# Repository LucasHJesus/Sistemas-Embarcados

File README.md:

# PAINEL SOLAR SEGUIDOR DE SOL
# (SUN TRACKING SOLAR PANEL)
## Projeto final da matéria de sistemas embarcados

Lucas Humberto Jesus de Lima - 12011ECP011

Bruno Pavan Ciriani da SIlva - 12011ECP012

## Objetivo
 
  O projeto tem como finalidade a construção de um circuito que controla a
rotação(posição relativa) de um painel solar baseado na incidência luminosa, de forma a
maximizar a irradiação na superfície da placa. Tal tarefa é realizada por meio da utilização de
sensores LDR(posicionados nas bordas da placa), cuja medição serve de referência para
rotação em torno do eixo de um servo motor.
Dados como energia gerada em tempo real serão monitorados, exibidos em um display
LCD e armazenados em uma memória externa.

## Principais Requisitos
Para o funcionamento adequado do projeto, existem certos requisitos, como os
seguintes componentes:

* Painel Solar
* Microcontrolador STM32F411CE
* 2 Sensores LDR
* 3 Resistores de 10kΩ
* Servo Motor
* Push Button (NA)
* Placa para apoio do painel solar
* Fios de conexão
* Bateria 9V
* Regulador de Tensão
* Display LCD
* Memória externa e adaptador
* Resistores para medição da energia gerada
  As funções dos principais componentes são:

  Painel Solar : Transforma energia luminosa em energia elétrica.
  
 STM32F411CE: Microcontrolador usado para comparar os sinais enviados e coordenar o
funcionamento dos demais componentes do projeto.

 Sensores LDR: Geram diferentes valores de resistência de acordo com a incidência de luz solar
sobre eles, para serem comparados pelo microcontrolador.
  
 Servo Motor: Rotaciona a placa na direção desejada.

 Push Button: Habilita(ou desabilita) a alimentação do circuito.

 Bateria 9V: Alimentar os componentes do circuito.
  
 Regulador de Tensão: Regula o valor de tensão para o valor usado pelos componentes do
circuito.

  Display: Exibe dados de interesse coletados pelo circuito medidor em tempo real.

  Memória Externa: Armazena dados de interesse coletados pelo circuito medidor.

  Resistores para medição da energia gerada: Divisor de tensão com o intuito de limitar o valor
em 3.3V para que possa ser medido pelo microcontrolador.

## Diagrama de blocos

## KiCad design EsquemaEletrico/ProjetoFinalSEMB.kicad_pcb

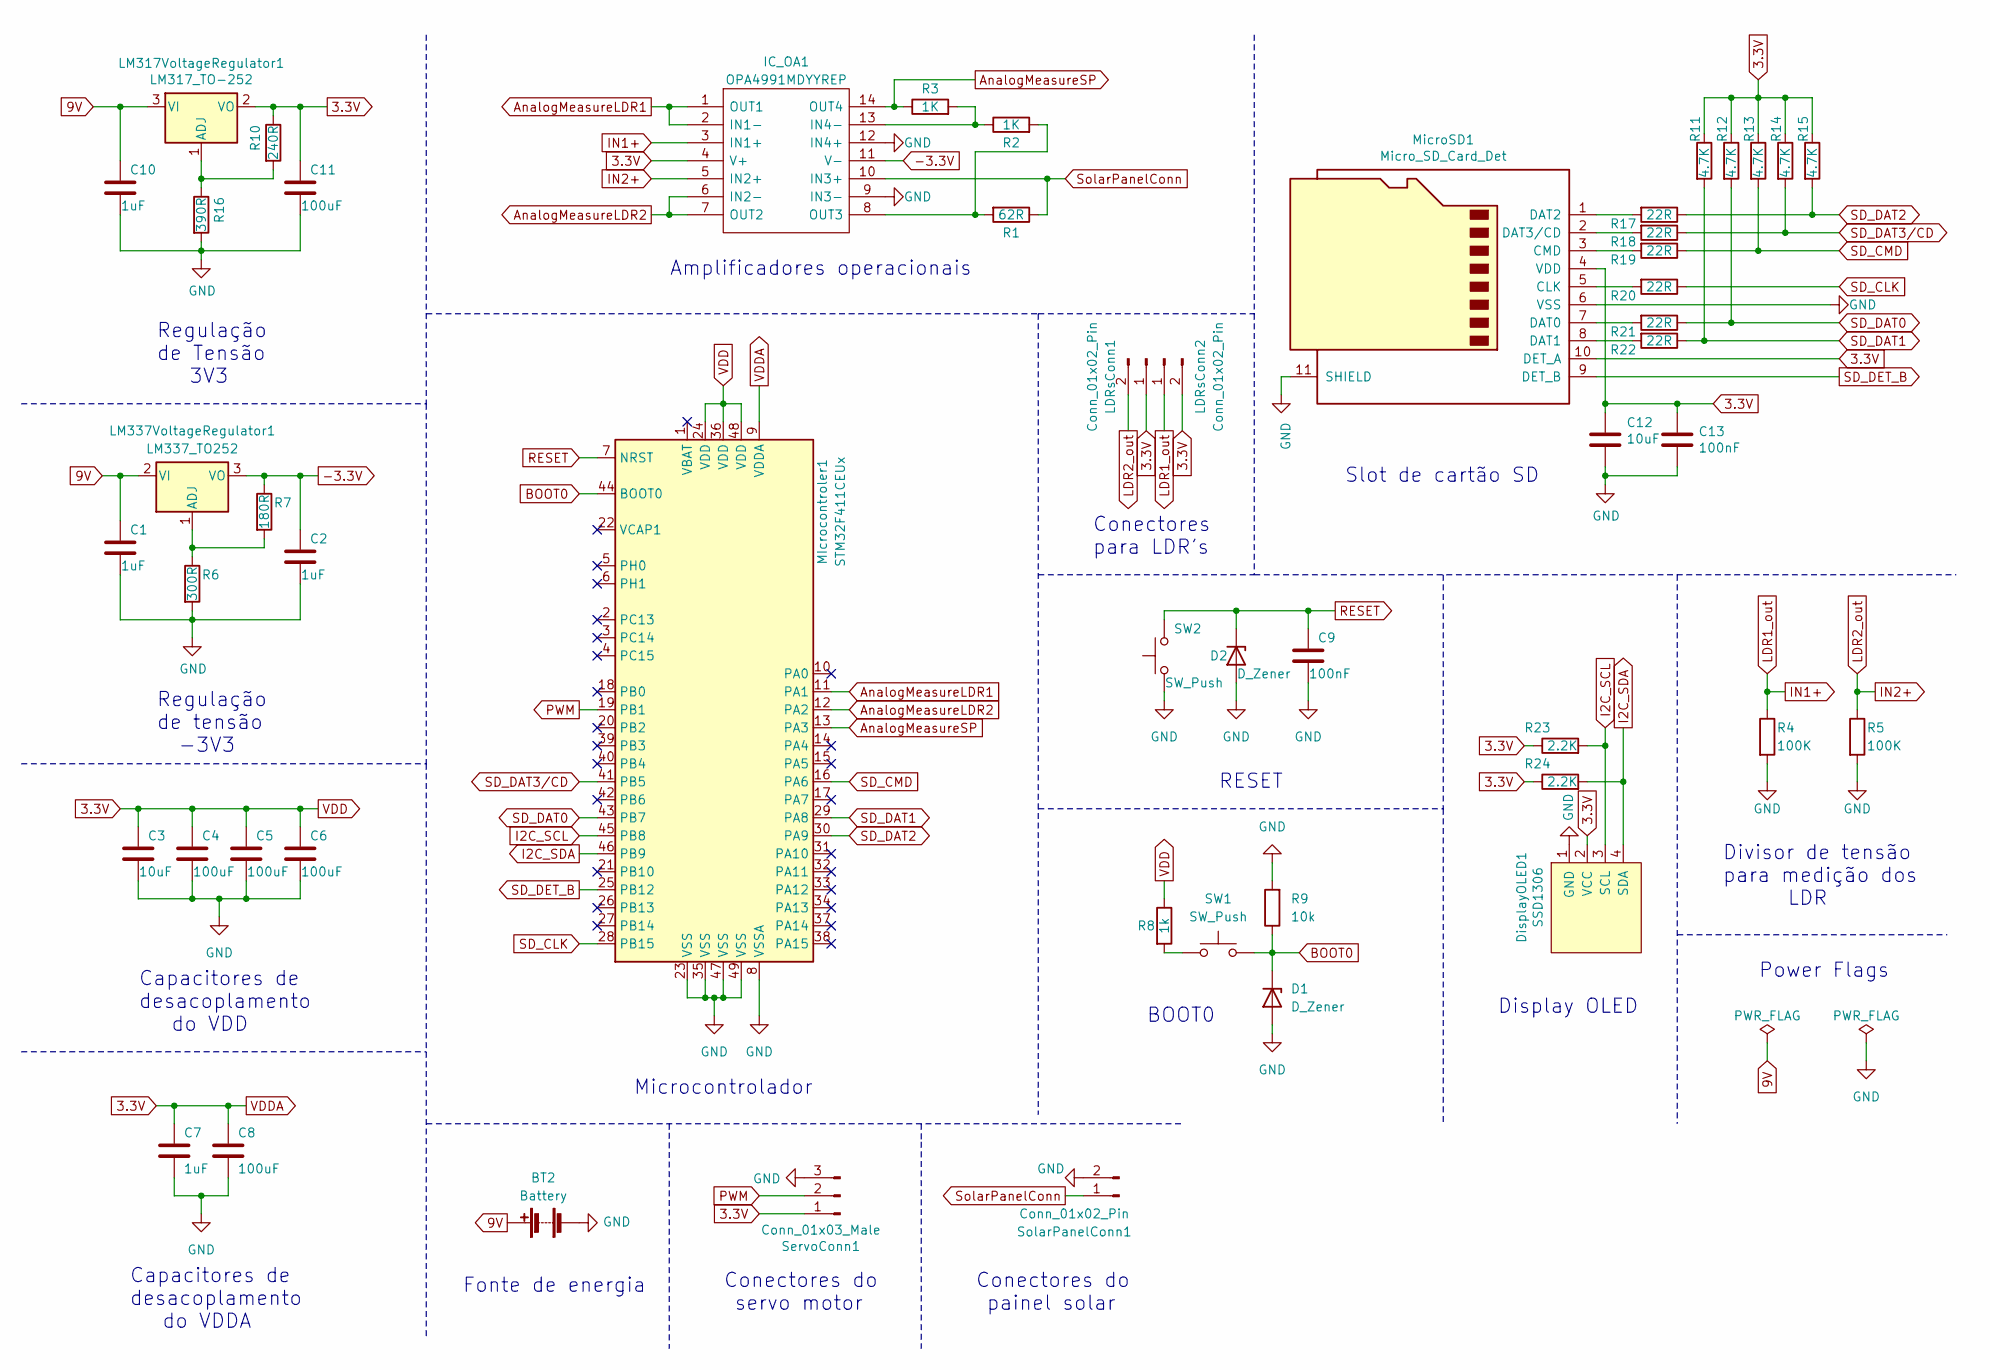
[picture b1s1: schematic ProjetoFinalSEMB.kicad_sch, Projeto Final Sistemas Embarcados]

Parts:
BT2: Battery; 12BH611GR
C1, C2, C7, C10: 1uF; C2220_FT
C3, C12: 10uF; capacitor10u
C4, C5, C6, C8: 100uF; CAPC3225X279N
C9, C13: 100nF; C1206
C11: 100uF; C1206
D1, D2: D_Zener; diode
DisplayOLED1: SSD1306; 128x64OLED
IC_OA1: OPA4991MDYYREP; SOP65P640X120-14N; Mouser Part Number 595-OPA4991MDYYREP
LDRsConn1, LDRsConn2: Conn_01x02_Pin; 10129380902001ALF
LM317VoltageRegulator1: LM317_TO-252; TO-252-2
LM337VoltageRegulator1: LM337_TO252; TO-252-2
MIcrocontroler1: STM32F411CEUx; QFN-48-1EP_7x7mm_P0.5mm_EP5.6x5.6mm
MicroSD1: Micro_SD_Card_Det; microSD_HC_Hirose_DM3D-SF
R1: 62R; ERJ1T__2512_
R2, R3: 1K; ERJ1T__2512_
R4, R5: 100K; ERA8KEB1004V
R6: 300R; ERJ1T__2512_
R7: 180R; ERJ1T__2512_
R8: 1k; ERJ1T__2512_
R9: 10k; ERA8KEB1004V
R10: 240R; ERJ1T__2512_
R11, R12, R13, R14, R15: 4.7K; ERJ1T__2512_
R16: 390R; ERJ1T__2512_
R17, R18, R19, R20, R21, R22: 22R; ERJL12__1812_
R23, R24: 2.2K; ERJ1T__2512_
SW1, SW2: SW_Push; push_button
ServoConn1: Conn_01x03_Male; 10129380903001BLF
SolarPanelConn1: Conn_01x02_Pin; 10129380902001ALF

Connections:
3.3V: C3.1, C4.1, C5.1, C6.1, C7.1, C8.1, C11.1, C12.1, C13.1, DisplayOLED1.2 (VCC), IC_OA1.4 (V+), LDRsConn1.1, LDRsConn2.2, LM317VoltageRegulator1.2 (VO), MIcrocontroler1.9 (VDDA), MIcrocontroler1.24 (VDD), MIcrocontroler1.36 (VDD), MIcrocontroler1.48 (VDD), MicroSD1.4 (VDD), MicroSD1.10 (DET_A), R8.1, R10.1, R11.1, R12.1, R13.1, R14.1, R15.1, R23.1, R24.1, ServoConn1.1
9V: BT2.1 (+), C1.1, C10.1, LM317VoltageRegulator1.3 (VI), LM337VoltageRegulator1.2 (VI)
-3.3V: C2.1, IC_OA1.11 (V-), LM337VoltageRegulator1.3 (VO), R7.1
AnalogMeasureLDR1: IC_OA1.1 (OUT1), IC_OA1.2 (IN1-), MIcrocontroler1.11 (PA1)
AnalogMeasureLDR2: IC_OA1.6 (IN2-), IC_OA1.7 (OUT2), MIcrocontroler1.12 (PA2)
AnalogMeasureSP: IC_OA1.14 (OUT4), MIcrocontroler1.13 (PA3), R3.1
BOOT0: D1.1 (K), MIcrocontroler1.44 (BOOT0), R9.1, SW1.2
GND: BT2.2 (-), C1.2, C2.2, C3.2, C4.2, C5.2, C6.2, C7.2, C8.2, C9.2, C10.2, C11.2, C12.2, C13.2, D1.2 (A), D2.2 (A), DisplayOLED1.1 (GND), IC_OA1.9 (IN3-), IC_OA1.12 (IN4+), MIcrocontroler1.8 (VSSA), MIcrocontroler1.23 (VSS), MIcrocontroler1.35 (VSS), MIcrocontroler1.47 (VSS), MIcrocontroler1.49 (VSS), MicroSD1.6 (VSS), MicroSD1.11 (SHIELD), R4.2, R5.2, R6.2, R9.2, R16.2, SW2.1, ServoConn1.3, SolarPanelConn1.2
I2C_SCL: DisplayOLED1.3 (SCL), MIcrocontroler1.45 (PB8), R23.2
I2C_SDA: DisplayOLED1.4 (SDA), MIcrocontroler1.46 (PB9), R24.2
IN1+: IC_OA1.3 (IN1+), LDRsConn2.1, R4.1
IN2+: IC_OA1.5 (IN2+), LDRsConn1.2, R5.1
unnamed: IC_OA1.13 (IN4-), R2.1, R3.2
unnamed: IC_OA1.8 (OUT3), R1.2, R2.2
unnamed: LM317VoltageRegulator1.1 (ADJ), R10.2, R16.1
unnamed: LM337VoltageRegulator1.1 (ADJ), R6.1, R7.2
unnamed: MicroSD1.5 (CLK), R20.2
unnamed: MicroSD1.3 (CMD), R19.2
unnamed: MicroSD1.7 (DAT0), R21.2
unnamed: MicroSD1.8 (DAT1), R22.2
unnamed: MicroSD1.1 (DAT2), R17.2
unnamed: MicroSD1.2 (DAT3/CD), R18.2
unnamed: R8.2, SW1.1
PWM: MIcrocontroler1.19 (PB1), ServoConn1.2
RESET: C9.1, D2.1 (K), MIcrocontroler1.7 (NRST), SW2.2
SD_CLK: MIcrocontroler1.28 (PB15), R20.1
SD_CMD: MIcrocontroler1.16 (PA6), R13.2, R19.1
SD_DAT0: MIcrocontroler1.43 (PB7), R12.2, R21.1
SD_DAT1: MIcrocontroler1.29 (PA8), R11.2, R22.1
SD_DAT2: MIcrocontroler1.30 (PA9), R15.2, R17.1
SD_DAT3/CD: MIcrocontroler1.41 (PB5), R14.2, R18.1
SD_DET_B: MIcrocontroler1.25 (PB12), MicroSD1.9 (DET_B)
SolarPanelConn: IC_OA1.10 (IN3+), R1.1, SolarPanelConn1.1

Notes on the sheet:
Conectores para LDR's
Microcontrolador
Conectores do painel solar
Fonte de energia
Slot de cartão SD
Display OLED
Power Flags
BOOT0
Capacitores de desacoplamento do VDDA
Regulação de Tensão 3V3
Conectores do servo motor
Capacitores de desacoplamento do VDD
Regulação de tensão -3V3
Divisor de tensão para medição dos LDR
RESET
Amplificadores operacionais

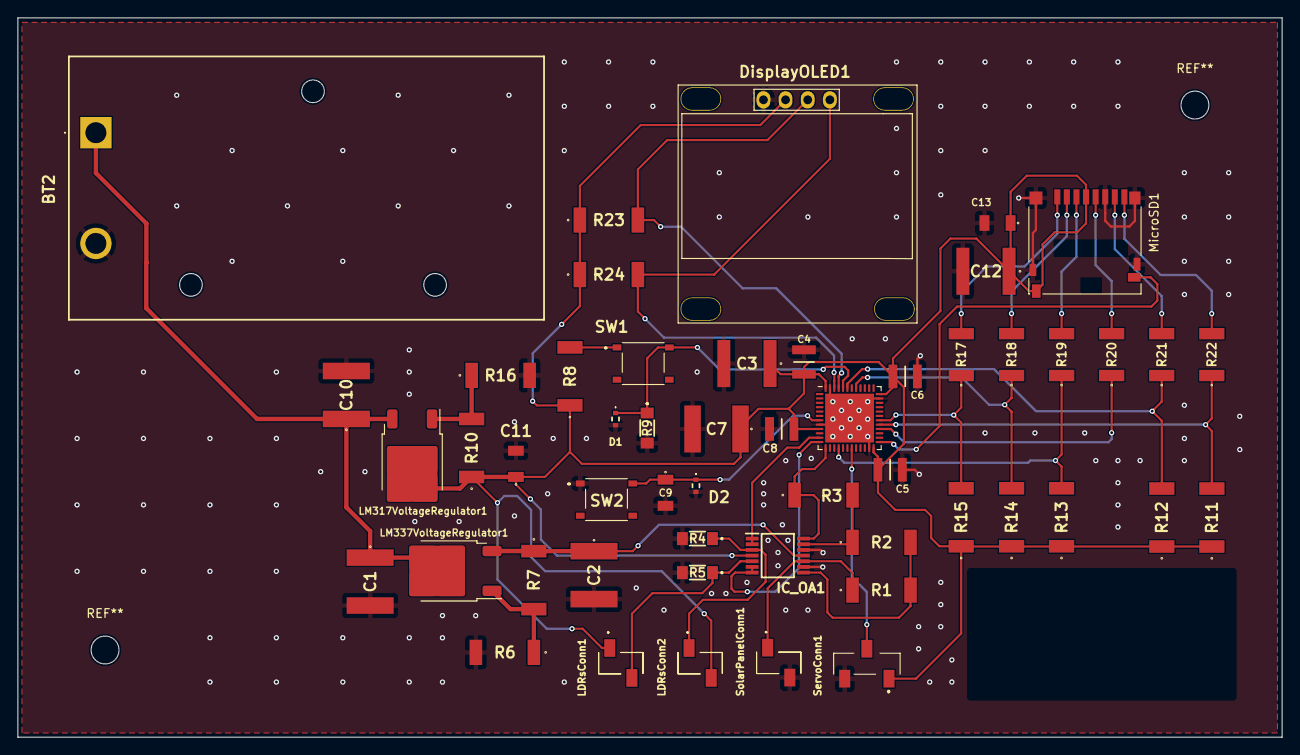
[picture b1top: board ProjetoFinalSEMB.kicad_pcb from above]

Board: 2 copper layers, 145.0 x 82.5 mm, 52 parts (0 on the bottom side), 33 nets.

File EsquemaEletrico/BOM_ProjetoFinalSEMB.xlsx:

| Item | Qty | Reference(s) | Descrição | Part Number (Mouser) | Preço Unitario($) | Preço total($) | Footprint | Observações | Link
 | 1 | 1 | BT1 | Suporte para bateria de 9V | 12BH611-GR | 1.35 | 1.35 | Footprints:12BH611GR | None | https://br.mouser.com/ProductDetail/Eagle-Plastic-Devices/12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
 | 2 | 4 | C1, C2, C7,C10 | Capacitor de 1uF | C2220X105K2RACAUTO | 3.19 | 12.76 | Footprints:C2220_FT | None | https://br.mouser.com/ProductDetail/KEMET/C2220X105K2RACAUTO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
 | 3 | 2 | C3, C12 | Capacitor de 10uF | C2220C106J5RACTU | 4.91 | 9.82 | SamacSys_Parts:capacitor10u | None | https://br.mouser.com/ProductDetail/KEMET/C2220C106J5RACTU?q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
 | 4 | 4 | C4, C5, C6, C8 | Capacitor de 100uF | 12106G107ZAT2A | 1.17 | 4.68 | Footprints:CAPC3225X279N | None | https://br.mouser.com/ProductDetail/KYOCERA-AVX/12106G107ZAT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
 | 5 | 3 | C9, C13,C11 | Capacitor de 0,1uF | C1206C104J1RACAUTO | 0.26 | 0.78 | Footprints:C1206 | None | https://br.mouser.com/ProductDetail/KEMET/C1206C104J1RACAUTO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
 | 6 | 2 | D1, D2 | Diodo Zener | BZX58550-C6V8-QX | 0.38 | 0.76 | Footprints:diode | None | https://br.mouser.com/ProductDetail/Nexperia/BZX58550-C6V8-Q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
 | 7 | 1 | DisplayOLED1 | Display OLED | SSD1306 | 7.27 | 7.27 | Footprints:128x64OLED | Amazon | https://www.amazon.com/SSD1306/s?k=SSD1306
 | 8 | 1 | IC_OA1 | CI de Amplificadores Operacionais | LM324BIPWR | 0.55000000000000004 | 0.55000000000000004 | Footprints:SOP65P640X120-14N | None | https://br.mouser.com/ProductDetail/Texas-Instruments/LM324B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
 | 9 | 2 | LDRsConn1,LDRsConn1 | 2 pinos de conexão | 10129380-902001ALF | 0.15 | 0.3 | Footprints:10129380902001ALF | None | https://br.mouser.com/ProductDetail/Amphenol-FCI/10129380-90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
 | 10 | 1 | LM317VoltageRegulator1 | Regulador de Tensão | LM317MDT-TR | 0.93 | 0.93 | Package_TO_SOT_SMD:TO-252-2 | None | https://br.mouser.com/ProductDetail/STMicroelectronics/LM317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
 | 11 | 1 | LM337VoltageRegulator1 | Regulador de Tensão | LM337KVURG3 | 1.05 | 1.05 | Package_TO_SOT_SMD:TO-252-2 | None | https://br.mouser.com/ProductDetail/Texas-Instruments/LM337K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
 | 12 | 1 | MIcrocontroler1 | Microcontrolador | STM32F411CEU7 | 7.48 | 7.48 | Package_DFN_QFN:QFN-48-1EP_7x7mm_P0.5mm_EP5.6x5.6mm | None | https://br.mouser.com/ProductDetail/STMicroelectronics/STM32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
 | 13 | 1 | MicroSD1 | Slot de cartão SD | MICRO-SD-CARD | 0.52 | 0.52 | Connector_Card:microSD_HC_Hirose_DM3D-SF | None | https://br.mouser.com/ProductDetail/Olimex-Ltd/MICRO-SD-CARD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
 | 14 | 1 | R1 | Resistor de 62R (1%) | ERJ-1TNF62R0U | 1.18 | 1.18 | Footprints:ERJ1T__2512_ | None | https://br.mouser.com/ProductDetail/Panasonic/ERJ-1TNF62R0U?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
 | 15 | 3 | R2, R3, R8 | Resistores de 1K (1%) | ERJ-1TNF1001U | 0.7 | 2.0999999999999996 | Footprints:ERJ1T__2512_ | None | https://br.mouser.com/ProductDetail/Panasonic/ERJ-1TNF1001U?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
 | 16 | 2 | R4, R5 | Resistores de 100k (0.1%) | ERA-8VRB1003V | 1.32 | 2.64 | Footprints:ERA8KEB1004V | None | https://br.mouser.com/ProductDetail/Panasonic/ERA-8VRB1003V?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
 | 17 | 1 | R6 | Resistor de 300R (1%) | ERJ-1TNF3000U | 0.52 | 0.52 | Footprints:ERJ1T__2512_ | None | https://br.mouser.com/ProductDetail/Panasonic/ERJ-1TNF3000U?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
 | 18 | 1 | R7 | Resistor de 180R (1%) | ERJ-1TNF1800U | 1.18 | 1.18 | Footprints:ERJ1T__2512_ | None | https://br.mouser.com/ProductDetail/Panasonic/ERJ-1TNF1800U?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
 | 19 | 1 | R9 | Resistor de 10K (0.1%) | ERA-8VRB1002V | 1.32 | 1.32 | Footprints:ERA8KEB1004V | None | https://br.mouser.com/ProductDetail/Panasonic/ERA-8VRB1002V?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
 | 20 | 1 | R10 | Resistor de 240R (1%) | ERJ-1TNF2400U | 1.18 | 1.18 | Footprints:ERJ1T__2512_ | None | https://br.mouser.com/ProductDetail/Panasonic/ERJ-1TNF2400U?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
 | 21 | 5 | R11, R12, R13, R14, R15 | Resistores de 4.7k (1%) | ERJ-1TNF4701U | 0.7 | 3.5 | Footprints:ERJ1T__2512_ | None | https://br.mouser.com/ProductDetail/Panasonic/ERJ-1TNF4701U?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
 | 22 | 1 | R16 | Resistor de 390R (1%) | ERJ-1TNF3900U | 0.7 | 0.7 | Footprints:ERJ1T__2512_ | None | https://br.mouser.com/ProductDetail/Panasonic/ERJ-1TNF3900U?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
 | 23 | 6 | R17, R18, R19, R20, R21, R22 | Resistores de 22R (1%) | ERJ-L12KF22MU | 0.75 | 4.5 | Footprints:ERJL12__1812_ | None | https://br.mouser.com/ProductDetail/Panasonic/ERJ-L12KF22MU?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
 | 24 | 2 | R23, R24 | Resistores de 2.2K (1%) | ERJ-1TNF2201U | 1.17 | 2.34 | Footprints:ERJ1T__2512_ | None | https://br.mouser.com/ProductDetail/Panasonic/ERJ-1TNF2201U?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
 | 25 | 1 | ServoConn1 | 3 pinos de conexão | 1012938090301BLF | 0.12 | 0.12 | Footprints:10129380903001BLF | None | https://br.mouser.com/ProductDetail/Amphenol-FCI/10129380-90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
 | 26 | 1 | SolarPanelConn1 | 2 pinos de conexão | 10129380-902001ALF | 0.15 | 0.15 | Footprints:10129380902001ALF | None | https://br.mouser.com/ProductDetail/Amphenol-FCI/10129380-90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
 | 27 | 2 | SW1, SW2 | Botões para Boot e Reset | PTS526SM08SMTR2L | 0.13 | 0.26 | Footprints:push_button | None | https://br.mouser.com/ProductDetail/CK/PTS526-SM08-SMTR2-LFS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
 |  |  |  |  | Total | 40.330000000000005 | 69.940000000000012

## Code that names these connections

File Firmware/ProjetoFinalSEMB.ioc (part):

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Mcu.Name=STM32F411C(C-E)Ux
Mcu.Package=UFQFPN48
Mcu.UserName=STM32F411CEUx
PA1.GPIOParameters=GPIO_Label
PA1.GPIO_Label=LRD1_MEASURE
PA1.Signal=SharedAnalog_PA1
PA13.Mode=Serial_Wire
PA13.Signal=SYS_JTMS-SWDIO
PA14.Mode=Serial_Wire
PA14.Signal=SYS_JTCK-SWCLK
PA2.GPIOParameters=GPIO_Label
PA2.GPIO_Label=LRD2_MEASURE
PA2.Signal=SharedAnalog_PA2
PA3.GPIOParameters=GPIO_Label
PA3.GPIO_Label=SP_MEASURE
PA3.Signal=SharedAnalog_PA3
PA6.Mode=SD_4_bits_Wide_bus
PA6.Signal=SDIO_CMD
PA8.Mode=SD_4_bits_Wide_bus
PA8.Signal=SDIO_D1
PA9.Mode=SD_4_bits_Wide_bus
PA9.Signal=SDIO_D2
PB1.Signal=S_TIM3_CH4
PB12.Signal=GPIO_Input
PB15.Mode=SD_4_bits_Wide_bus
PB15.Signal=SDIO_CK
PB5.Mode=SD_4_bits_Wide_bus
PB5.Signal=SDIO_D3
PB7.Mode=SD_4_bits_Wide_bus
PB7.Signal=SDIO_D0
PB8.Mode=I2C
PB8.Signal=I2C1_SCL
PB9.Mode=I2C
PB9.Signal=I2C1_SDA
PH0\ -\ OSC_IN.Mode=HSE-External-Oscillator
PH0\ -\ OSC_IN.Signal=RCC_OSC_IN
PH1\ -\ OSC_OUT.Mode=HSE-External-Oscillator
PH1\ -\ OSC_OUT.Signal=RCC_OSC_OUT
RCC.HSE_VALUE=25000000
RCC.SYSCLKFreq_VALUE=100000000
RCC.SYSCLKSource=RCC_SYSCLKSOURCE_PLLCLK
board=custom

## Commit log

2023-06-15 adição do esquema eletrico e firmware feitos para a primeira entrega
2023-06-15 some fixes
2023-07-14 Projeto final completo
